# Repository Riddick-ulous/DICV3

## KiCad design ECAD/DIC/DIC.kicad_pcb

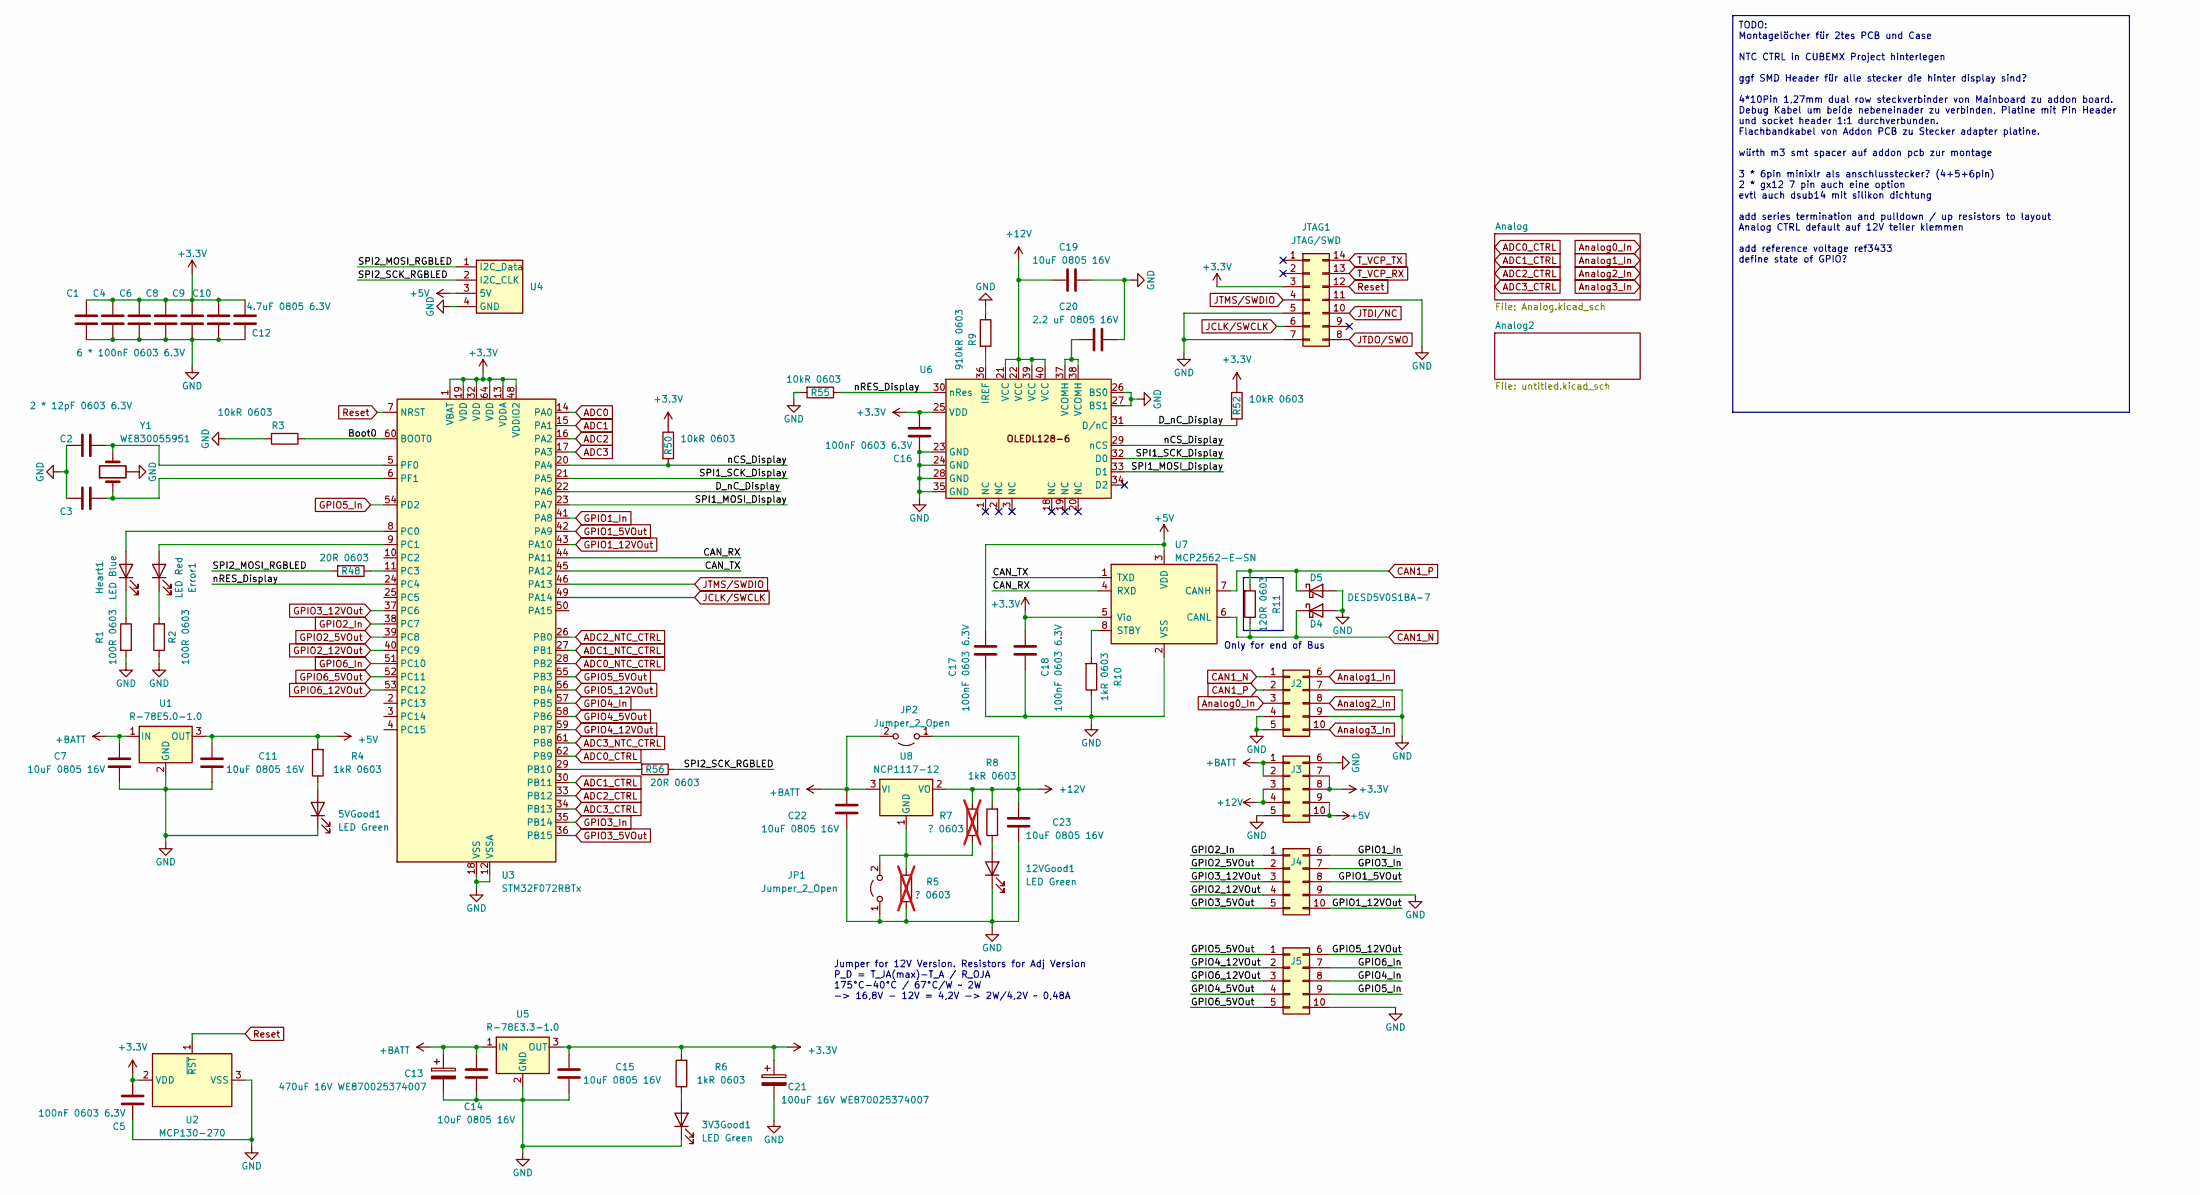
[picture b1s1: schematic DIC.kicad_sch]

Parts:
3V3Good1, 5VGood1, 12VGood1: LED Green; LED_0805_2012Metric_Pad1.15x1.40mm_HandSolder
C1, C4, C5, C6, C8, C10, C16, C17, C18: 100nF 0603 6.3V; C_0603_1608Metric_Pad1.08x0.95mm_HandSolder
C2: 12pF 0603 6.3V; C_0603_1608Metric_Pad1.08x0.95mm_HandSolder
C3: 2 * 12pF 0603 6.3V; C_0603_1608Metric_Pad1.08x0.95mm_HandSolder
C7, C11, C14, C15, C19, C22, C23: 10uF 0805 16V; C_0805_2012Metric_Pad1.18x1.45mm_HandSolder
C9: 6 * 100nF 0603 6.3V; C_0603_1608Metric_Pad1.08x0.95mm_HandSolder
C12: 4.7uF 0805 6.3V; C_0805_2012Metric_Pad1.18x1.45mm_HandSolder
C13: 470uF 16V WE870025374007; CP_Radial_D8.0mm_P3.50mm
C20: 2.2 uF 0805 16V; C_0805_2012Metric_Pad1.18x1.45mm_HandSolder
C21: 100uF 16V WE870025374007; CP_Radial_D8.0mm_P3.50mm
D4, D5: DESD5V0S1BA-7; D_SOD-323
Error1: LED Red; LED_0805_2012Metric_Pad1.15x1.40mm_HandSolder
Heart1: LED Blue; LED_0805_2012Metric_Pad1.15x1.40mm_HandSolder
J2, J3, J4, J5: Conn_02x05_Top_Bottom; PinHeader_2x05_P1.27mm_Vertical
JP1, JP2: Jumper_2_Open; SolderJumper-2_P1.3mm_Open_RoundedPad1.0x1.5mm
JTAG1: JTAG/SWD; PinHeader_2x07_P1.27mm_Vertical
R1, R2: 100R 0603; R_0603_1608Metric_Pad0.98x0.95mm_HandSolder
R3, R50, R52, R55: 10kR 0603; R_0603_1608Metric_Pad0.98x0.95mm_HandSolder
R4, R6, R8, R10: 1kR 0603; R_0603_1608Metric_Pad0.98x0.95mm_HandSolder
R5, R7: ? 0603; R_0603_1608Metric_Pad0.98x0.95mm_HandSolder; not fitted
R9: 910kR 0603; R_0603_1608Metric_Pad0.98x0.95mm_HandSolder
R11: 120R 0603; R_0603_1608Metric_Pad0.98x0.95mm_HandSolder
R48, R56: 20R 0603; R_0603_1608Metric_Pad0.98x0.95mm_HandSolder
U1: R-78E5.0-1.0; Converter_DCDC_RECOM_R-78E-0.5_THT
U2: MCP130-270; SOT-23
U3: STM32F072RBTx; LQFP-64_10x10mm_P0.5mm
U4: LED_Ring
U5: R-78E3.3-1.0; Converter_DCDC_RECOM_R-78E-0.5_THT
U6: EA OLEDL128-6
U7: MCP2562-E-SN; SOIC-8_3.9x4.9mm_P1.27mm
U8: NCP1117-12; TO-252-2
Y1: WE830055951; Oscillator_SMD_EuroQuartz_XO32-4Pin_3.2x2.5mm_HandSoldering

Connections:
+3.3V: C1.1, C4.1, C5.2, C6.1, C8.1, C9.1, C10.1, C12.1, C15.1, C16.2, C18.2, C21.1, J3.7, J3.8, JTAG1.3, R6.2, R50.1, R52.1, U2.2 (VDD), U3.1 (VBAT), U3.13 (VDDA), U3.19 (VDD), U3.32 (VDD), U3.48 (VDDIO2), U3.64 (VDD), U5.3 (OUT), U6.25 (VDD), U7.5 (Vio); also elsewhere on the board
+5V: C11.1, C17.2, J3.9, J3.10, R4.2, U1.3 (OUT), U4.3 (5V), U7.3 (VDD); also elsewhere on the board
+12V: C19.2, C23.1, J3.3, J3.4, JP2.1 (A), R7.2, R8.2, U6.21 (VCC), U6.22 (VCC), U6.39 (VCC), U6.40 (VCC), U8.2 (VO)
+BATT: C7.1, C13.1, C14.1, C22.1, J3.1, J3.2, JP2.2 (B), U1.1 (IN), U5.1 (IN), U8.3 (VI)
/Boot0: R3.1, U3.60 (BOOT0)
/CAN_RX: U3.44 (PA11), U7.4 (RXD)
/CAN_TX: U3.45 (PA12), U7.1 (TXD)
/D_nC_Display: R52.2, U3.22 (PA6), U6.31 (D/nC)
/SPI1_MOSI_Display: U3.23 (PA7), U6.33 (D1)
/SPI1_SCK_Display: U3.21 (PA5), U6.32 (D0)
/SPI2_MOSI_RGBLED: R48.2, U4.1 (I2C_Data)
/SPI2_SCK_RGBLED: R56.1, U4.2 (I2C_CLK)
/nCS_Display: R50.2, U3.20 (PA4), U6.29 (nCS)
/nRES_Display: R55.1, U3.24 (PC4), U6.30 (nRes)
ADC0: U3.14 (PA0); also elsewhere on the board
ADC0_CTRL: U3.62 (PB9); also elsewhere on the board
ADC0_NTC_CTRL: U3.28 (PB2); also elsewhere on the board
ADC1: U3.15 (PA1); also elsewhere on the board
ADC1_CTRL: U3.30 (PB11); also elsewhere on the board
ADC1_NTC_CTRL: U3.27 (PB1); also elsewhere on the board
ADC2: U3.16 (PA2); also elsewhere on the board
ADC2_CTRL: U3.33 (PB12); also elsewhere on the board
ADC2_NTC_CTRL: U3.26 (PB0); also elsewhere on the board
ADC3: U3.17 (PA3); also elsewhere on the board
ADC3_CTRL: U3.34 (PB13); also elsewhere on the board
ADC3_NTC_CTRL: U3.61 (PB8); also elsewhere on the board
Analog0_In: J2.3; also elsewhere on the board
Analog1_In: J2.6; also elsewhere on the board
Analog2_In: J2.8; also elsewhere on the board
Analog3_In: J2.10; also elsewhere on the board
CAN1_N: D4.1 (K), J2.1, R11.1, U7.6 (CANL)
CAN1_P: D5.1 (K), J2.2, R11.2, U7.7 (CANH)
GND: 3V3Good1.1 (K), 5VGood1.1 (K), 12VGood1.1 (K), C1.2, C2.1, C3.1, C4.2, C5.1, C6.2, C7.2, C8.2, C9.2, C10.2, C11.2, C12.2, C13.2, C14.2, C15.2, C16.1, C17.1, C18.1, C19.1, C20.1, C21.2, C22.2, C23.2, D4.2 (A), D5.2 (A), J2.4, J2.5, J2.7, J2.9, J3.5, J3.6, J4.9, J5.10, JP1.1 (A), JTAG1.5, JTAG1.7, JTAG1.11, R1.2, R2.1, R3.2, R5.1, R9.1, R10.1, R55.2, U1.2 (GND), U2.3 (VSS), U3.12 (VSSA), U3.18 (VSS), U3.31 (VSS), U3.47 (VSS), U3.63 (VSS), U4.4 (GND), U5.2 (GND), U6.23 (GND), U6.24 (GND), U6.26 (BS0), U6.27 (BS1), U6.28 (GND), U6.35 (GND), U7.2 (VSS), Y1.2 (2_GND), Y1.4 (4_GND); also elsewhere on the board
GPIO1_5VOut: J4.8, U3.42 (PA9)
GPIO1_12VOut: J4.10, U3.43 (PA10)
GPIO1_In: J4.6, U3.41 (PA8)
GPIO2_5VOut: J4.2, U3.39 (PC8)
GPIO2_12VOut: J4.4, U3.40 (PC9)
GPIO2_In: J4.1, U3.38 (PC7)
GPIO3_5VOut: J4.5, U3.36 (PB15)
GPIO3_12VOut: J4.3, U3.37 (PC6)
GPIO3_In: J4.7, U3.35 (PB14)
GPIO4_5VOut: J5.4, U3.58 (PB6)
GPIO4_12VOut: J5.2, U3.59 (PB7)
GPIO4_In: J5.8, U3.57 (PB5)
GPIO5_5VOut: J5.1, U3.55 (PB3)
GPIO5_12VOut: J5.6, U3.56 (PB4)
GPIO5_In: J5.9, U3.54 (PD2)
GPIO6_5VOut: J5.5, U3.52 (PC11)
GPIO6_12VOut: J5.3, U3.53 (PC12)
GPIO6_In: J5.7, U3.51 (PC10)
JCLK/SWCLK: JTAG1.6, U3.49 (PA14)
JTDI/NC: JTAG1.10
JTDO/SWO: JTAG1.8
JTMS/SWDIO: JTAG1.4, U3.46 (PA13)
unnamed: 3V3Good1.2 (A), R6.1
unnamed: 5VGood1.2 (A), R4.1
unnamed: 12VGood1.2 (A), R8.1
unnamed: C20.2, U6.37 (VCOMH), U6.38 (VCOMH)
unnamed: Error1.2 (A), U3.9 (PC1)
unnamed: Error1.1 (K), R2.2
unnamed: Heart1.2 (A), U3.8 (PC0)
unnamed: Heart1.1 (K), R1.1
unnamed: JP1.2 (B), R5.2, R7.1, U8.1 (GND)
unnamed: R56.2, U3.29 (PB10)
unnamed: R48.1, U3.11 (PC3)
unnamed: C2.2, U3.5 (PF0), Y1.3 (3_Crystal)
unnamed: C3.2, U3.6 (PF1), Y1.1 (1_Crystal)
unnamed: R9.2, U6.36 (IREF)
unnamed: R10.2, U7.8 (STBY)
Reset: JTAG1.12, U2.1 (~RST), U3.7 (NRST)
T_VCP_RX: JTAG1.13
T_VCP_TX: JTAG1.14

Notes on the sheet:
TODO: Montagelöcher für 2tes PCB und Case NTC CTRL in CUBEMX Project hinterlegen ggf SMD Header für alle stecker die hinter display sind? 4*10Pin 1,27mm dual row steckverbinder von Mainboard zu addon board. Debug Kabel um beide nebeneinader zu verbinden, Platine mit Pin Header und socket header 1:1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
Only for end of Bus
Jumper for 12V Version. Resistors for Adj Version P_D = T_JA(max)-T_A / R_OJA 175°C-40°C / 67°C/W ~ 2W -> 16,8V - 12V = 4,2V -> 2W/4,2V ~ 0,48A

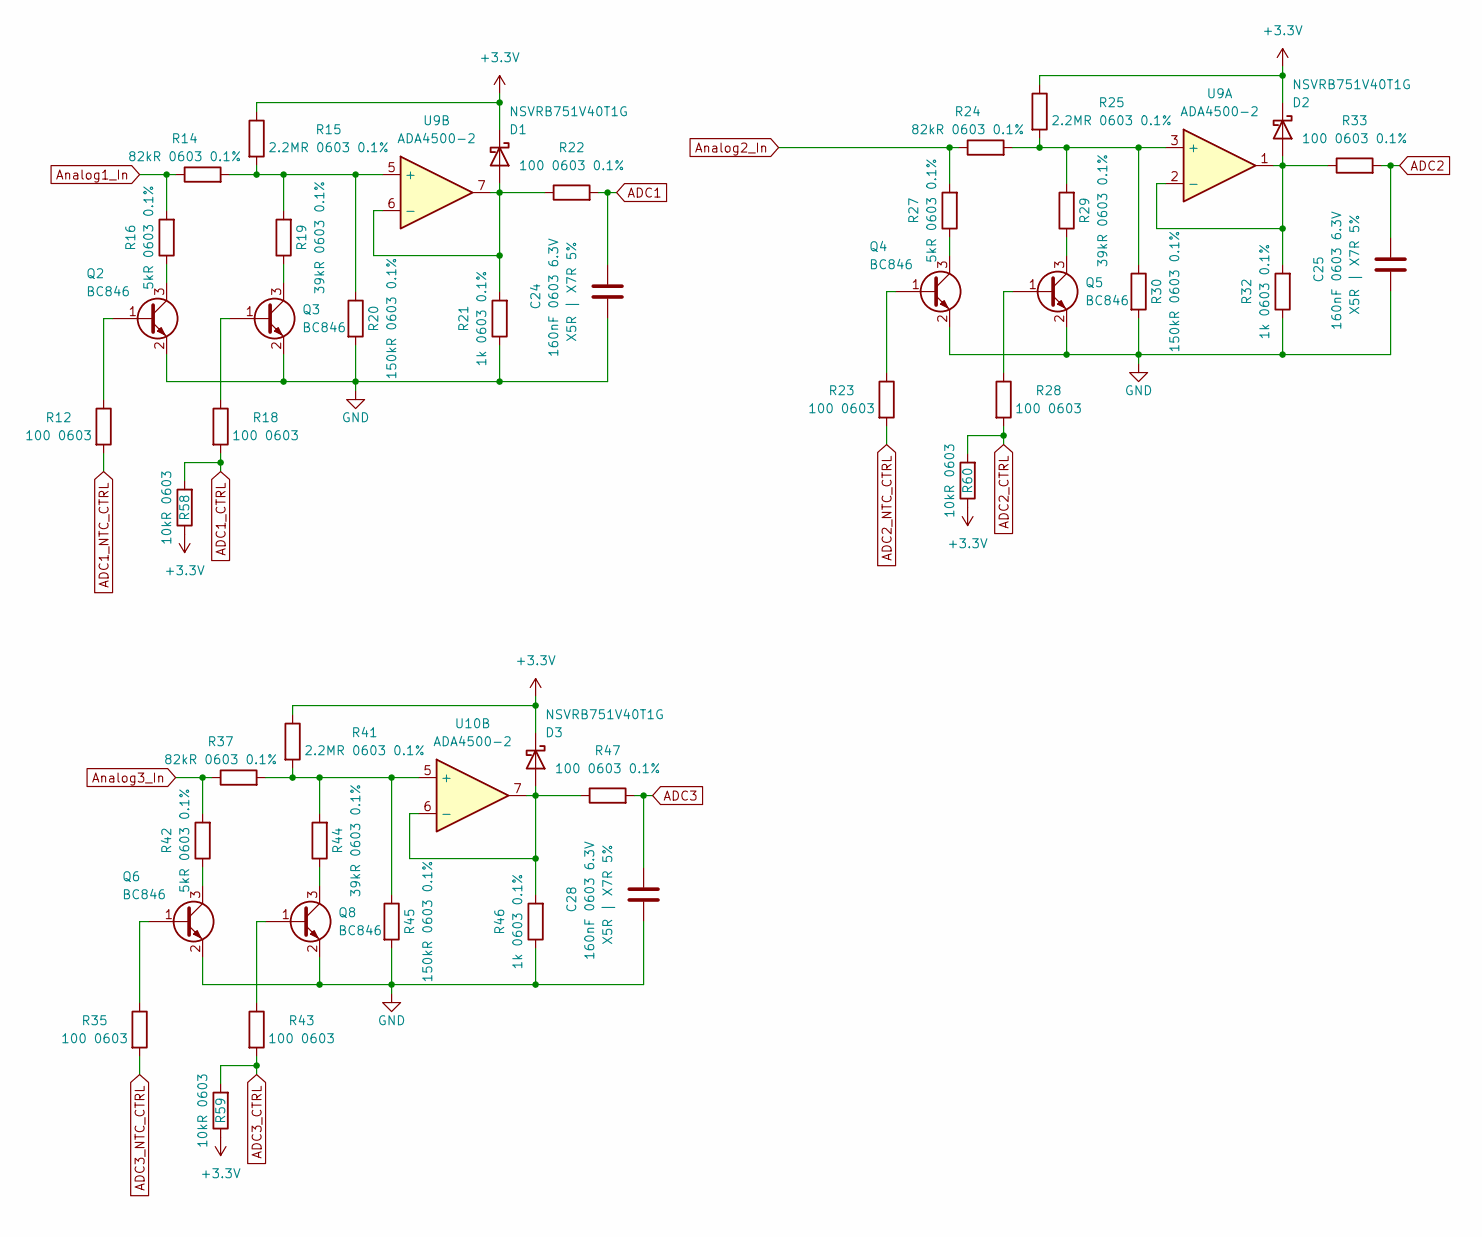
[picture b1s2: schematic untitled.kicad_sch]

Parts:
C24, C25, C28: 160nF 0603 6.3V; C_0603_1608Metric_Pad1.08x0.95mm_HandSolder; PartNr. VJ0603Y223JXJAC
D1, D2, D3: NSVRB751V40T1G; D_SOD-323_HandSoldering; PartNr. NSVRB751V40T1G
Q2, Q3, Q4, Q5, Q6, Q8: BC846; SOT-23
R12, R18, R23, R28, R35, R43: 100 0603; R_0603_1608Metric_Pad0.98x0.95mm_HandSolder
R14, R24, R37: 82kR 0603 0.1%; R_0603_1608Metric_Pad0.98x0.95mm_HandSolder
R15, R25, R41: 2.2MR 0603 0.1%; R_0603_1608Metric_Pad0.98x0.95mm_HandSolder
R16, R27, R42: 5kR 0603 0.1%; R_0603_1608Metric_Pad0.98x0.95mm_HandSolder
R19, R29, R44: 39kR 0603 0.1%; R_0603_1608Metric_Pad0.98x0.95mm_HandSolder
R20, R30, R45: 150kR 0603 0.1%; R_0603_1608Metric_Pad0.98x0.95mm_HandSolder
R21, R32, R46: 1k 0603 0.1%; R_0603_1608Metric_Pad0.98x0.95mm_HandSolder
R22, R33, R47: 100 0603 0.1%; R_0603_1608Metric_Pad0.98x0.95mm_HandSolder
R58, R59, R60: 10kR 0603; R_0603_1608Metric_Pad0.98x0.95mm_HandSolder
U9, U10: ADA4500-2; MSOP-8_3x3mm_P0.65mm

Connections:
+3.3V: D1.1 (K), D2.1 (K), D3.1 (K), R15.1, R25.1, R41.1, R58.1, R59.1, R60.1; also elsewhere on the board
ADC1: C24.2, R22.2; also elsewhere on the board
ADC1_CTRL: R18.2, R58.2; also elsewhere on the board
ADC1_NTC_CTRL: R12.2; also elsewhere on the board
ADC2: C25.2, R33.2; also elsewhere on the board
ADC2_CTRL: R28.2, R60.2; also elsewhere on the board
ADC2_NTC_CTRL: R23.2; also elsewhere on the board
ADC3: C28.2, R47.2; also elsewhere on the board
ADC3_CTRL: R43.2, R59.2; also elsewhere on the board
ADC3_NTC_CTRL: R35.2; also elsewhere on the board
Analog1_In: R14.1, R16.2; also elsewhere on the board
Analog2_In: R24.1, R27.2; also elsewhere on the board
Analog3_In: R37.1, R42.2; also elsewhere on the board
GND: C24.1, C25.1, C28.1, Q2.2 (E), Q3.2 (E), Q4.2 (E), Q5.2 (E), Q6.2 (E), Q8.2 (E), R20.2, R21.1, R30.2, R32.1, R45.2, R46.1; also elsewhere on the board
unnamed: D1.2 (A), R21.2, R22.1, U9.6 (-), U9.7
unnamed: D2.2 (A), R32.2, R33.1, U9.1, U9.2 (-)
unnamed: D3.2 (A), R46.2, R47.1, U10.6 (-), U10.7
unnamed: Q2.1 (B), R12.1
unnamed: Q2.3 (C), R16.1
unnamed: Q3.1 (B), R18.1
unnamed: Q3.3 (C), R19.1
unnamed: Q4.1 (B), R23.1
unnamed: Q4.3 (C), R27.1
unnamed: Q5.1 (B), R28.1
unnamed: Q5.3 (C), R29.1
unnamed: Q6.1 (B), R35.1
unnamed: Q6.3 (C), R42.1
unnamed: Q8.1 (B), R43.1
unnamed: Q8.3 (C), R44.1
unnamed: R24.2, R25.2, R29.2, R30.1, U9.3 (+)
unnamed: R14.2, R15.2, R19.2, R20.1, U9.5 (+)
unnamed: R37.2, R41.2, R44.2, R45.1, U10.5 (+)

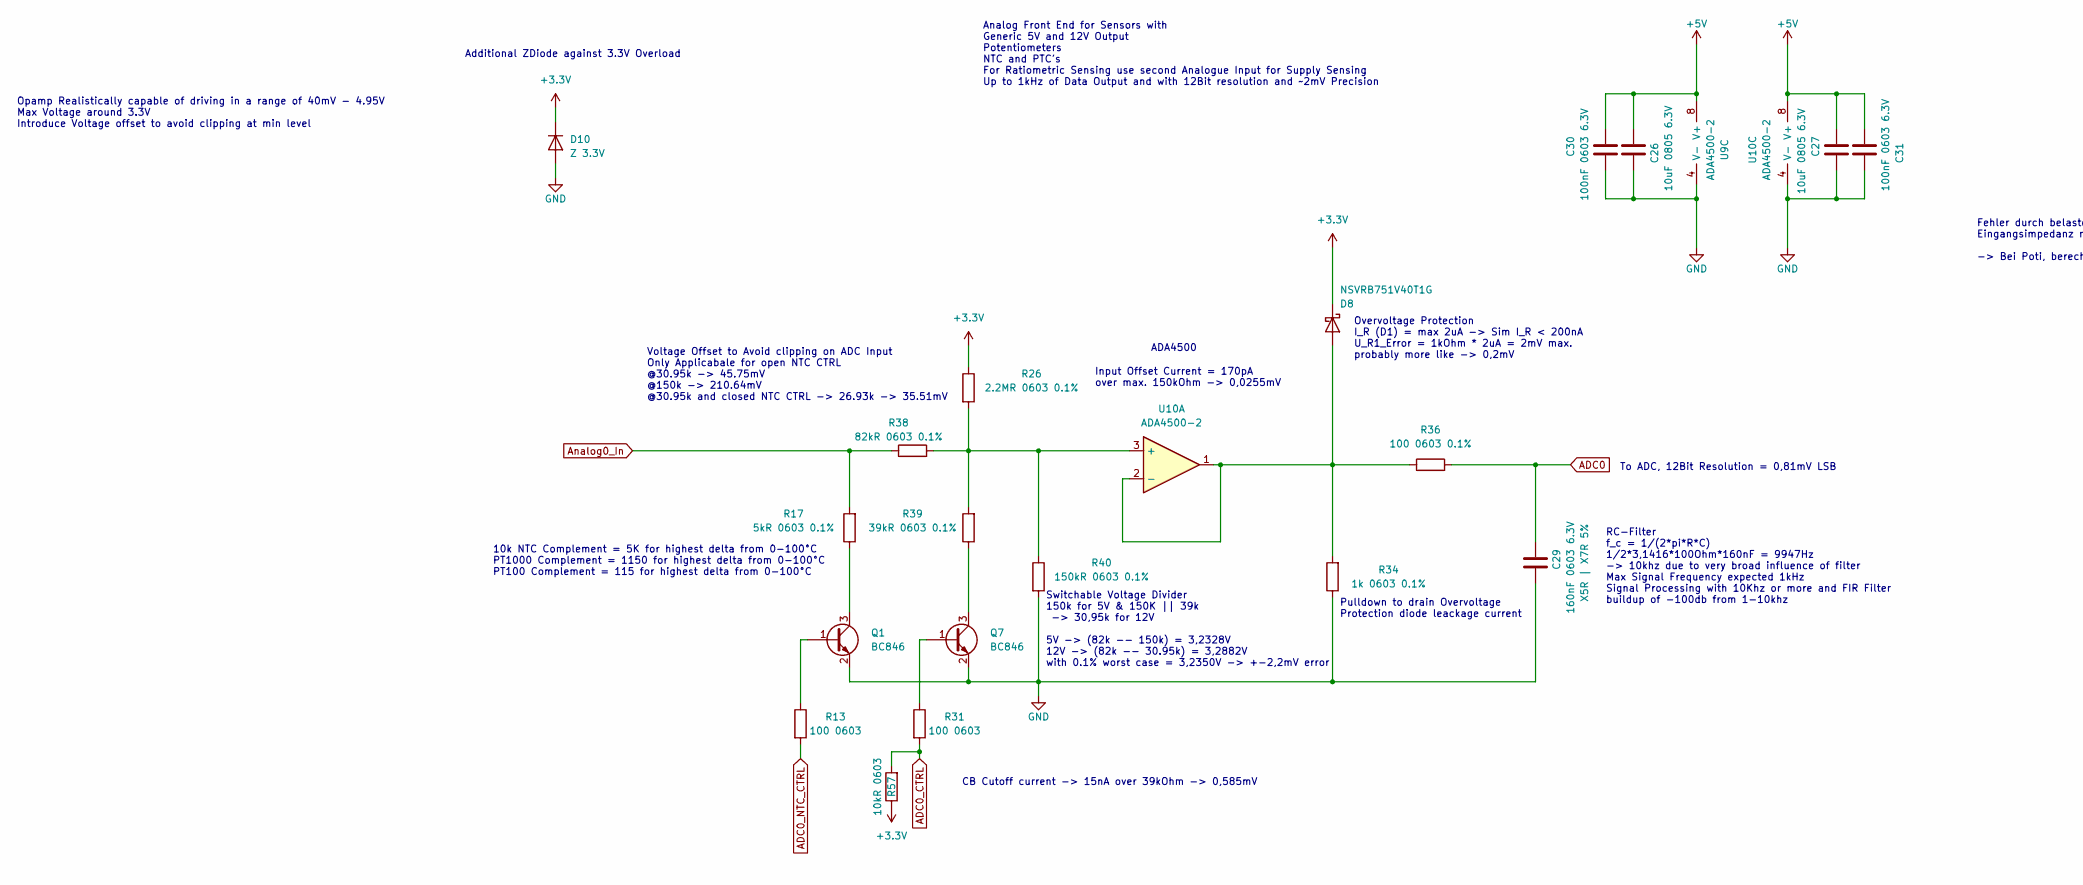
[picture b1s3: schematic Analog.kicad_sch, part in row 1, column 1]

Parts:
C26, C27: 10uF 0805 6.3V; C_0805_2012Metric_Pad1.18x1.45mm_HandSolder
C29: 160nF 0603 6.3V; C_0603_1608Metric_Pad1.08x0.95mm_HandSolder; PartNr. VJ0603Y223JXJAC
C30, C31: 100nF 0603 6.3V; C_0603_1608Metric_Pad1.08x0.95mm_HandSolder
D8: NSVRB751V40T1G; D_SOD-323_HandSoldering; PartNr. NSVRB751V40T1G
D10: Z 3.3V; D_SOD-323_HandSoldering; PartNr. MM3Z3V3T1G
Q1, Q7: BC846; SOT-23
R13, R31: 100 0603; R_0603_1608Metric_Pad0.98x0.95mm_HandSolder
R17: 5kR 0603 0.1%; R_0603_1608Metric_Pad0.98x0.95mm_HandSolder
R26: 2.2MR 0603 0.1%; R_0603_1608Metric_Pad0.98x0.95mm_HandSolder
R34: 1k 0603 0.1%; R_0603_1608Metric_Pad0.98x0.95mm_HandSolder
R36: 100 0603 0.1%; R_0603_1608Metric_Pad0.98x0.95mm_HandSolder
R38: 82kR 0603 0.1%; R_0603_1608Metric_Pad0.98x0.95mm_HandSolder
R39: 39kR 0603 0.1%; R_0603_1608Metric_Pad0.98x0.95mm_HandSolder
R40: 150kR 0603 0.1%; R_0603_1608Metric_Pad0.98x0.95mm_HandSolder
R57: 10kR 0603; R_0603_1608Metric_Pad0.98x0.95mm_HandSolder
U9, U10: ADA4500-2; MSOP-8_3x3mm_P0.65mm

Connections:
+3.3V: D8.1 (K), D10.1 (K), R26.1, R57.1; also elsewhere on the board
+5V: C26.1, C27.2, C30.2, C31.1, U9.8 (V+), U10.8 (V+); also elsewhere on the board
ADC0: C29.2, R36.2; also elsewhere on the board
ADC0_CTRL: R31.2, R57.2; also elsewhere on the board
ADC0_NTC_CTRL: R13.2; also elsewhere on the board
Analog0_In: R17.2, R38.1; also elsewhere on the board
GND: C26.2, C27.1, C29.1, C30.1, C31.2, D10.2 (A), Q1.2 (E), Q7.2 (E), R34.1, R40.2, U9.4 (V-), U10.4 (V-); also elsewhere on the board
unnamed: D8.2 (A), R34.2, R36.1, U10.1, U10.2 (-)
unnamed: Q1.1 (B), R13.1
unnamed: Q1.3 (C), R17.1
unnamed: Q7.1 (B), R31.1
unnamed: Q7.3 (C), R39.1
unnamed: R26.2, R38.2, R39.2, R40.1, U10.3 (+)

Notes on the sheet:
ADA4500
To ADC, 12Bit Resolution = 0,81mV LSB
CB Cutoff current -> 15nA over 39kOhm -> 0,585mV
Analog Front End for Sensors with Generic 5V and 12V Output Potentiometers NTC and PTC's For Ratiometric Sensing use second Analogue Input for Supply Sensing Up to 1kHz of Data Output and with 12Bit resolution and ~2mV Precision
Input Offset Current = 170pA over max. 150kOhm -> 0,0255mV
Overvoltage Protection I_R (D1) = max 2uA -> Sim I_R < 200nA U_R1_Error = 1kOhm * 2uA = 2mV max. probably more like -> 0,2mV
Pulldown to drain Overvoltage Protection diode leackage current
Switchable Voltage Divider 150k for 5V & 150K || 39k -> 30,95k for 12V 5V -> (82k -- 150k) = 3,2328V 12V -> (82k -- 30.95k) = 3,2882V with 0.1% worst case = 3,2350V -> +-2,2mV error
Additional ZDiode against 3.3V Overload
Opamp Realistically capable of driving in a range of 40mV - 4.95V Max Voltage around 3.3V Introduce Voltage offset to avoid clipping at min level
Voltage Offset to Avoid clipping on ADC Input Only Applicabale for open NTC CTRL @30.95k -> 45.75mV @150k -> 210.64mV @30.95k and closed NTC CTRL -> 26.93k -> 35.51mV
10k NTC Complement = 5K for highest delta from 0-100°C PT1000 Complement = 1150 for highest delta from 0-100°C PT100 Complement = 115 for highest delta from 0-100°C
Fehler durch belasteten spannungsteiler idr so groß das ohne impedanzwandler nicht praktikabel. Eingangsimpedanz muss bei 500k und größer liegen damit der Messfehler hinreichend klein wird. -> Bei Poti, berechung des Eingangswertes nur über belasteten spannungsteiler!!!
Abweichung durch belasteten SPannungsteiler so groß, das Dimensionierung der Eingangsimoedanz in bezug auf andere Abweichungsmechanismen nicht praktikabel -> Auswertung von Potis in SW nur über belasteten SPannungsteiler
RC-Filter f_c = 1/(2*pi*R*C) 1/2*3,1416*100Ohm*160nF = 9947Hz -> 10khz due to very broad influence of filter Max Signal Frequency expected 1kHz Signal Processing with 10Khz or more and FIR Filter buildup of -100db from 1-10khz

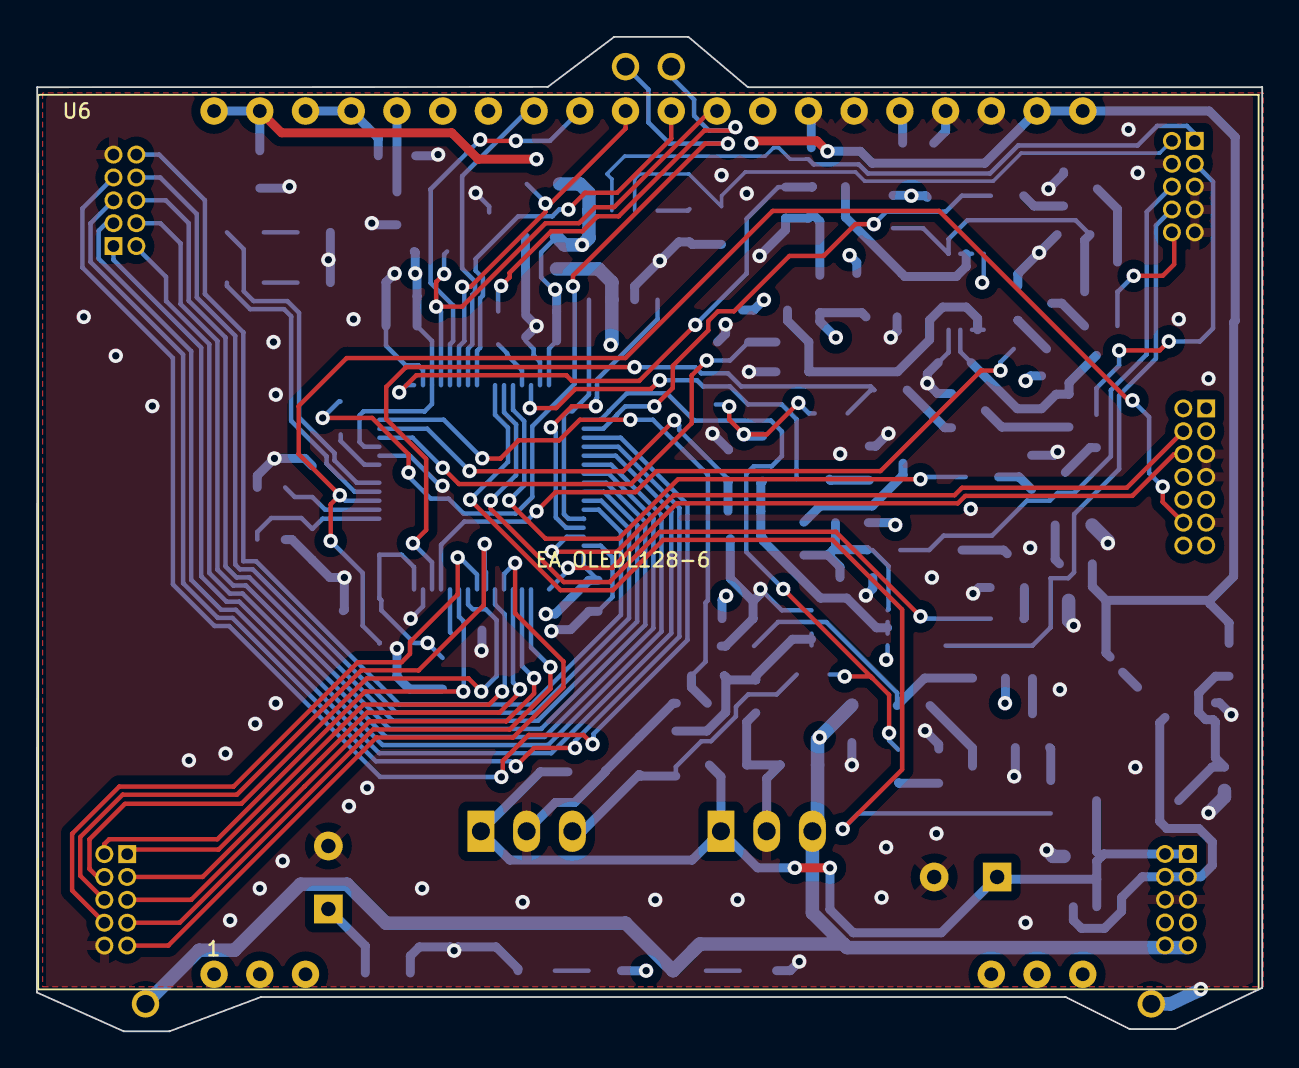
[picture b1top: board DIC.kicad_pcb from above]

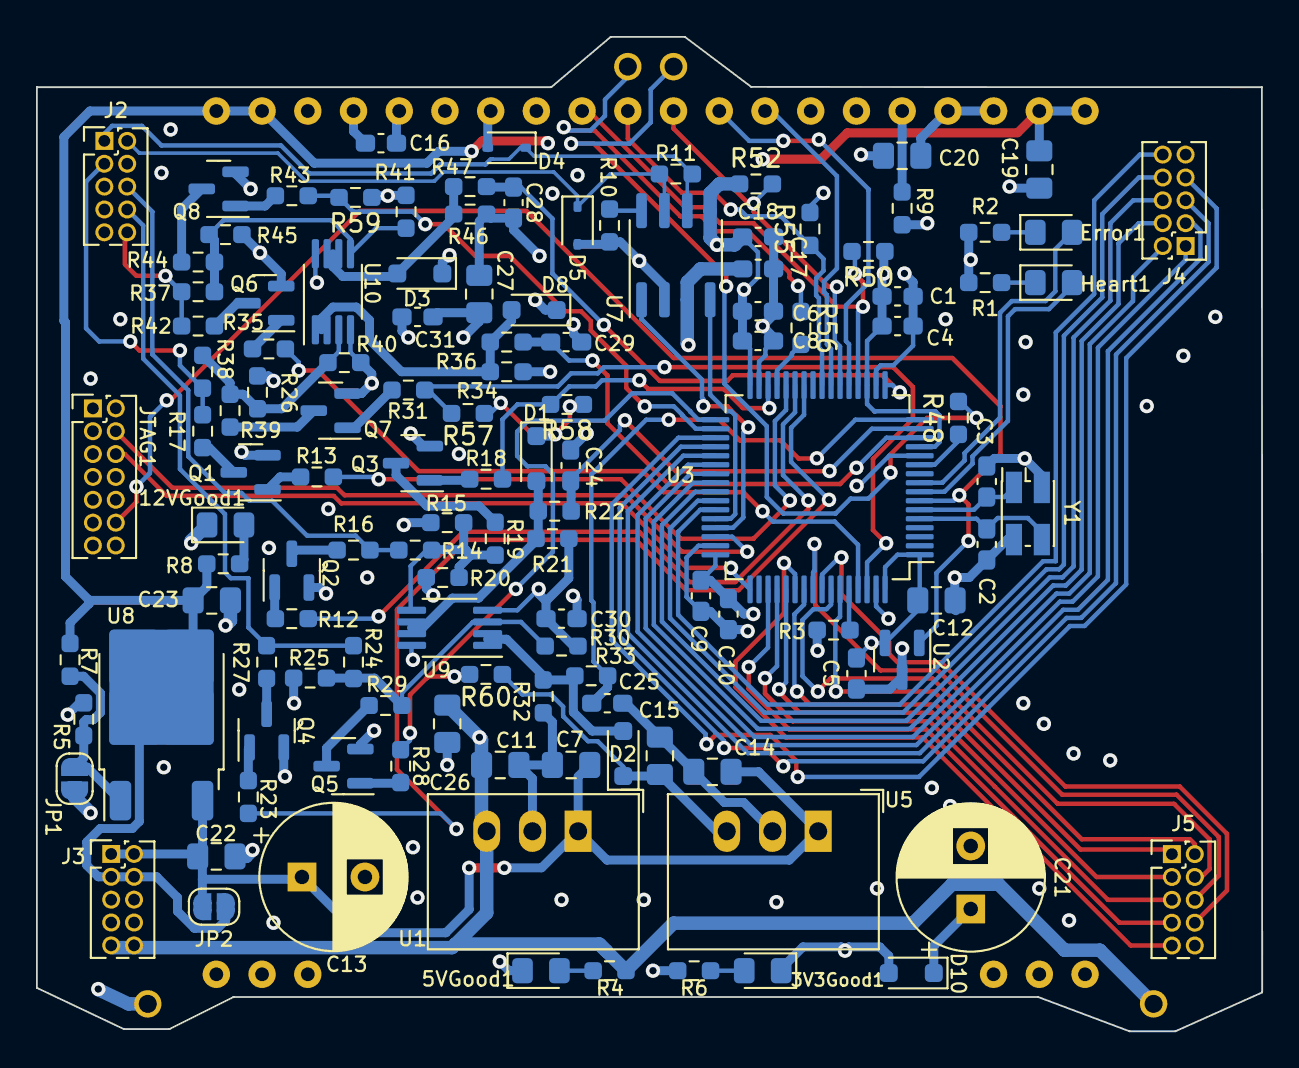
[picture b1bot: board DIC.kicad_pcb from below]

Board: 4 copper layers, 68.1 x 55.2 mm, 125 parts (123 on the bottom side), 93 nets.

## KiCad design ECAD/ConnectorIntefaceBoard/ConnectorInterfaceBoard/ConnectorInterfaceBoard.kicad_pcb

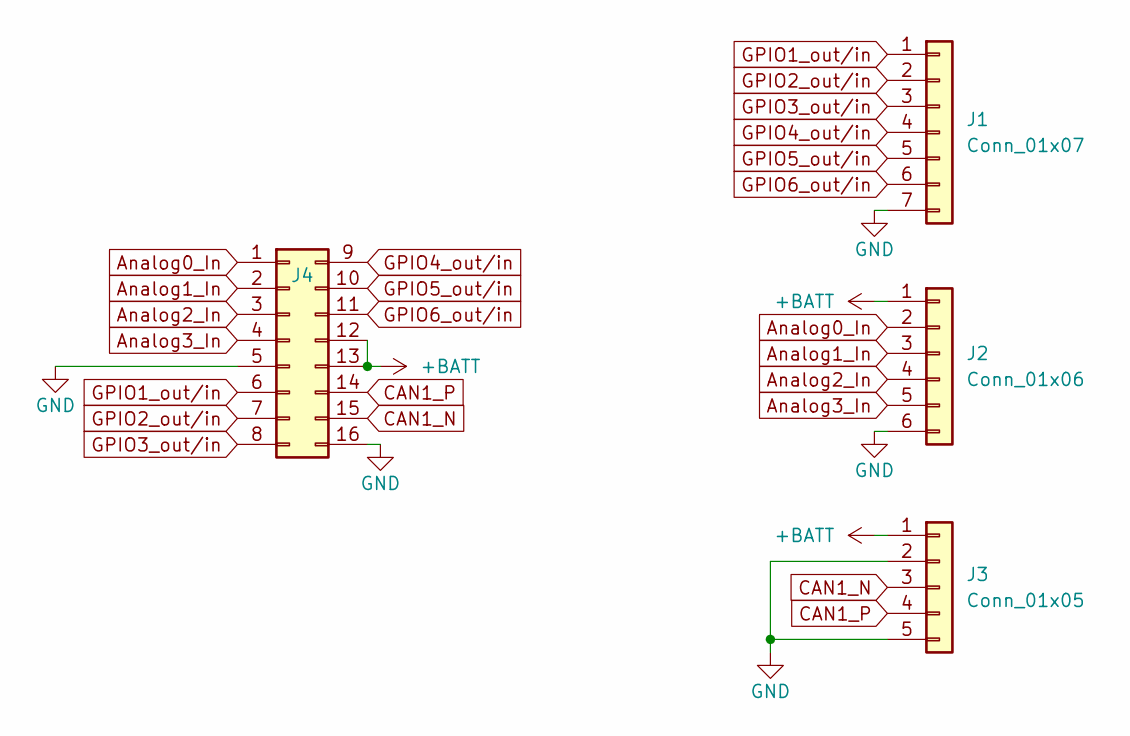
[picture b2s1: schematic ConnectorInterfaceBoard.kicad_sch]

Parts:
J1: Conn_01x07; MiniXLR_7Pin
J2: Conn_01x06; MiniXLR_6Pin
J3: Conn_01x05; MiniXLR_5Pin
J4: WE 62702621621; PinHeader_2x08_P1.27mm_Vertical

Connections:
+BATT: J2.1, J3.1, J4.12, J4.13
Analog0_In: J2.2, J4.1
Analog1_In: J2.3, J4.2
Analog2_In: J2.4, J4.3
Analog3_In: J2.5, J4.4
CAN1_N: J3.3, J4.15
CAN1_P: J3.4, J4.14
GND: J1.7, J2.6, J3.2, J3.5, J4.5, J4.16
GPIO1_out/in: J1.1, J4.6
GPIO2_out/in: J1.2, J4.7
GPIO3_out/in: J1.3, J4.8
GPIO4_out/in: J1.4, J4.9
GPIO5_out/in: J1.5, J4.10
GPIO6_out/in: J1.6, J4.11

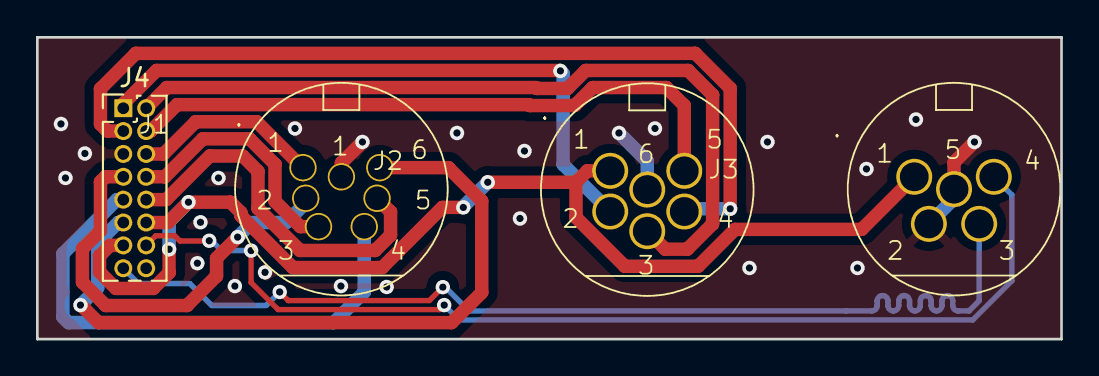
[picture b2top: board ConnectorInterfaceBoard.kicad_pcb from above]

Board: 2 copper layers, 56.9 x 16.8 mm, 4 parts (0 on the bottom side), 14 nets.
